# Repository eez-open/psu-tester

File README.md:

PCB tester for H24005 power supply's Power board r5B12 (or later) and AUX power module that can be used during PCBA and final quality assurance process. Require [Arduino Leonardo](https://www.arduino.cc/en/Main/ArduinoBoardLeonardo) board (attached on the opposite side of the PCB) and sketch with various test cases.

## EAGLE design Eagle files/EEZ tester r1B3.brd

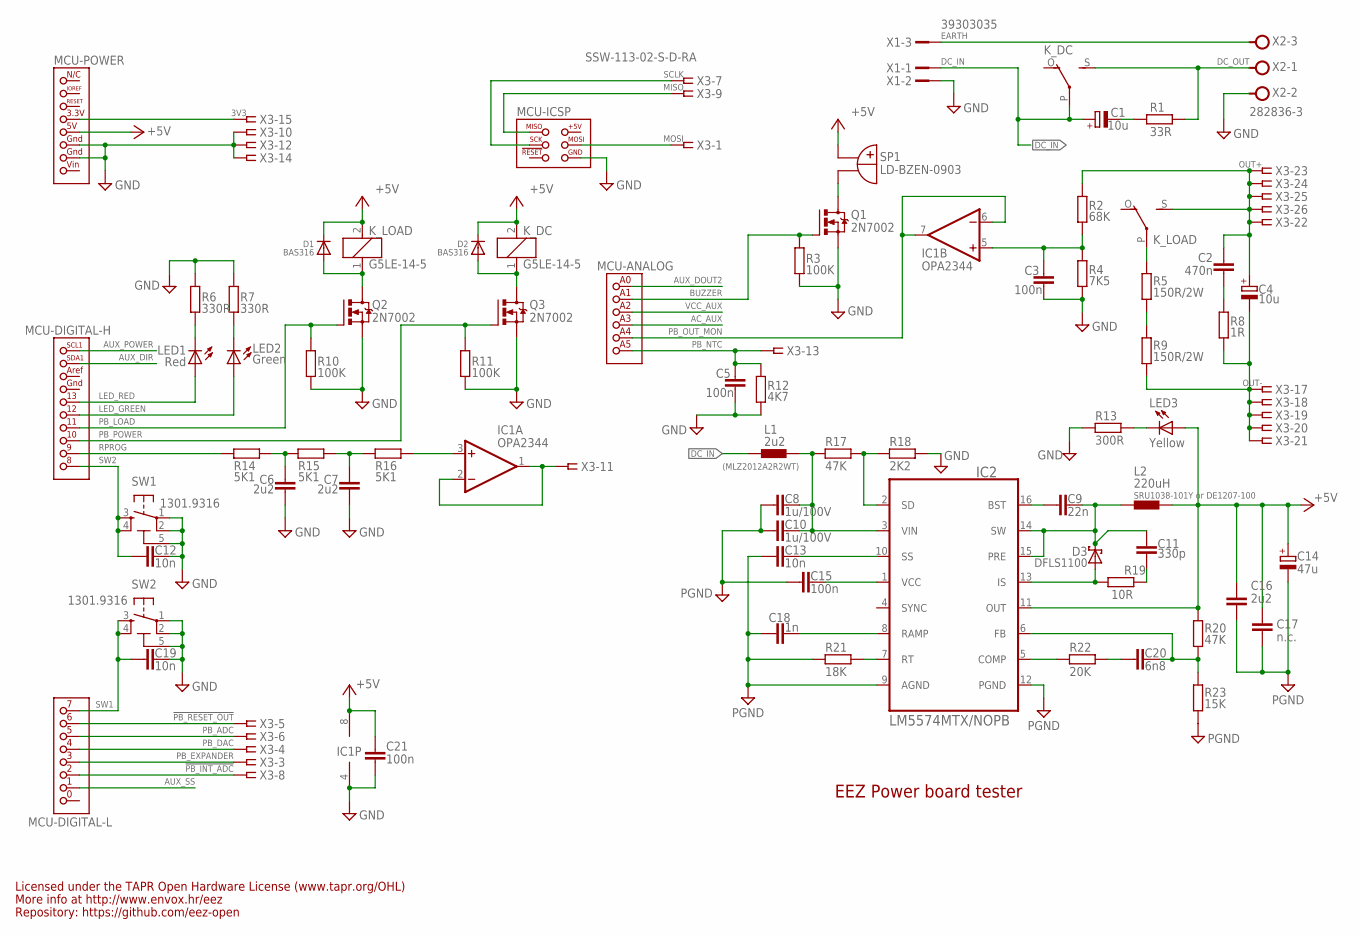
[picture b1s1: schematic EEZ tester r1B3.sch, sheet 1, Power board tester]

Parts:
C1, C4: 10u; PANASONIC_C
C2: 470n; C0805
C3, C5, C15, C21: 100n; C0603
C6, C7, C16: 2u2; C0805
C8, C10: 1u/100V; C1206
C9: 22n; C0805
C11: 330p; C0805
C12, C13, C19: 10n; C0805
C14: 47u; CAPAE660X610N
C17: n.c.; C0805
C18: 1n; C0805
C20: 6n8; C0805
D1, D2: BAS316; SOD323-W
D3: DFLS1100; SOD123
IC1: OPA2344; SOIC127P600X173-8N
IC2: LM5574MTX/NOPB; SOP65P640X110-16N
K_DC: G5LE-14-5; G5LE
K_LOAD: G5LE-14-5; G5LE
L1: 2u2; 0805
L2: 220uH; MSS1278
LED1: Red; LED3MM
LED2: Green; LED3MM
LED3: Yellow; LED3MM
MCU: ARDUINO_LEONARDO
Q1: 2N7002; SOT103P240X110-3N
Q2, Q3: 2N7002; SOT103P240X110-3N; MPN 2N7002-7-F
R1: 33R; R0805
R2: 68K; R0805
R3, R10, R11: 100K; R0805
R4: 7K5; R0805
R5, R9: 150R/2W; 0617/22
R6, R7: 330R; R0805
R8: 1R; R0805
R12: 4K7; R0805
R13: 300R; R0805
R14, R15, R16: 5K1; R0805
R17, R20: 47K; R0805
R18: 2K2; R0805
R19: 10R; R1206
R21: 18K; R0805
R22: 20K; R0805
R23: 15K; R0805
SP1: LD-BZEN-0903
SW1, SW2: 1301.9316; TACTM-6XN
X1: 39303035; MINIFIT_6659-3
X2: 282836-3; TBLOCK5.0_3
X3: SSW-113-02-S-D-RA; TSW-113-02-S-D-RA

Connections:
3V3: MCU.3.3V (3V3), X3.15
!PB_INT_ADC: MCU.2 (2(PE4)), X3.8
!PB_RESET_OUT: MCU.6 (6(PH3)), X3.5
+5V: C14.1 (+), C16.1, C17.1, C21.1, D1.C, D2.C, IC1.8 (V+), IC2.11 (OUT), K_DC.2, K_LOAD.2, L2.2, LED3.A, MCU.5V, R20.1, SP1.+B (+); also elsewhere on the board
AC_AUX: MCU.A3 (ADC3); also elsewhere on the board
AUX_DIR: MCU.SDA1; also elsewhere on the board
AUX_DOUT2: MCU.A0 (ADC0); also elsewhere on the board
AUX_POWER: MCU.SCL1; also elsewhere on the board
AUX_SS: MCU.1 (1(PE1)); also elsewhere on the board
AUX_USET: IC1.1 (OUT), IC1.2 (-IN), X3.11
BUZZER: MCU.A1 (ADC1), Q1.1 (G), R3.2
DC_IN: C1.1 (+), K_DC.P, L1.1, X1.1
DC_OUT: K_DC.S, R1.2, X2.1
DC_PREG1: C8.1, C10.1, IC2.3 (VIN), L1.2, R17.2
EARTH: X1.3, X2.3
GND: C3.1, C5.1, C6.2, C7.2, C8.2, C10.2, C12.2, C13.2, C14.2 (-), C15.1, C16.2, C17.2, C18.1, C19.2, C21.2, IC1.4 (V-), IC2.9 (AGND), IC2.12 (PGND), MCU.GND1, MCU.GND2, MCU.ICSP_GND (GND), Q1.2 (S), Q2.2 (S), Q3.2 (S), R3.1, R4.2, R6.2, R7.2, R10.1, R11.1, R12.2, R13.1, R18.1, R21.2, R23.2, SW1.1, SW1.2, SW1.5 (5-GND), SW2.1, SW2.2, SW2.5 (5-GND), X1.2, X2.2, X3.10, X3.12, X3.14; also elsewhere on the board
IS: D3.A, IC2.13 (IS), R19.1
LED_GREEN: LED2.A, MCU.12
LED_RED: LED1.A, MCU.13
MISO: MCU.ICSP_MISO (MISO), X3.9
MOSI: MCU.ICSP_MOSI (MOSI), X3.1
unnamed: R5.1, R9.2
unnamed: K_LOAD.P, R5.2
unnamed: LED3.K (C), R13.2
unnamed: C1.2 (-), R1.1
unnamed: C3.2, IC1.5 (+IN), R2.2, R4.1
unnamed: C7.1, R15.1, R16.2
unnamed: Q1.3 (D), SP1.-B (-)
unnamed: C6.1, R14.1, R15.2
unnamed: LED1.K (C), R6.1
unnamed: LED2.K (C), R7.1
unnamed: D2.A, K_DC.1, Q3.3 (D)
unnamed: D1.A, K_LOAD.1, Q2.3 (D)
unnamed: C11.2, R19.2
unnamed: C20.2, R22.2
unnamed: C2.2, R8.2
unnamed: C20.1, IC2.6 (FB), R20.2, R23.1
unnamed: C9.2, IC2.16 (BST)
unnamed: IC2.5 (COMP), R22.1
unnamed: IC2.7 (RT), R21.1
unnamed: C15.2, IC2.1 (VCC)
unnamed: C18.2, IC2.8 (RAMP)
unnamed: C13.1, IC2.10 (SS)
unnamed: IC2.2 (SD), R17.1, R18.2
unnamed: IC1.3 (+IN), R16.1
OUT+: C2.1, C4.1 (+), K_LOAD.S, R2.1, X3.22, X3.23, X3.24, X3.25, X3.26
OUT-: C4.2 (-), R8.1, R9.1, X3.17, X3.18, X3.19, X3.20, X3.21
PB_ADC: MCU.5 (5(PE3)), X3.6
PB_DAC: MCU.4 (4(PG5)), X3.4
PB_EXPANDER: MCU.3 (3(PE5)), X3.3
PB_LOAD: MCU.11, Q2.1 (G), R10.2
PB_NTC: C5.2, MCU.A5 (ADC5), R12.1, X3.13
PB_OUT_MON: IC1.6 (-IN), IC1.7 (OUT), MCU.A4 (ADC4)
PB_POWER: MCU.10, Q3.1 (G), R11.2
RPROG: MCU.9 (9(PH6)), R14.2
SCLK: MCU.ICSP_SCK (SCK), X3.7
SW: C9.1, C11.1, D3.C, IC2.14 (SW), IC2.15 (PRE), L2.1
SW1: C19.1, MCU.7 (7(PH4)), SW2.3, SW2.4
SW2: C12.1, MCU.8 (8(PH5)), SW1.3, SW1.4
VCC_AUX: MCU.A2 (ADC2); also elsewhere on the board

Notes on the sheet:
EEZ Power board tester
Licensed under the TAPR Open Hardware License (www.tapr.org/OHL)
Repository: https://github.com/eez-open
More info at http://www.envox.hr/eez
(MLZ2012A2R2WT)
SRU1038-101Y or DE1207-100

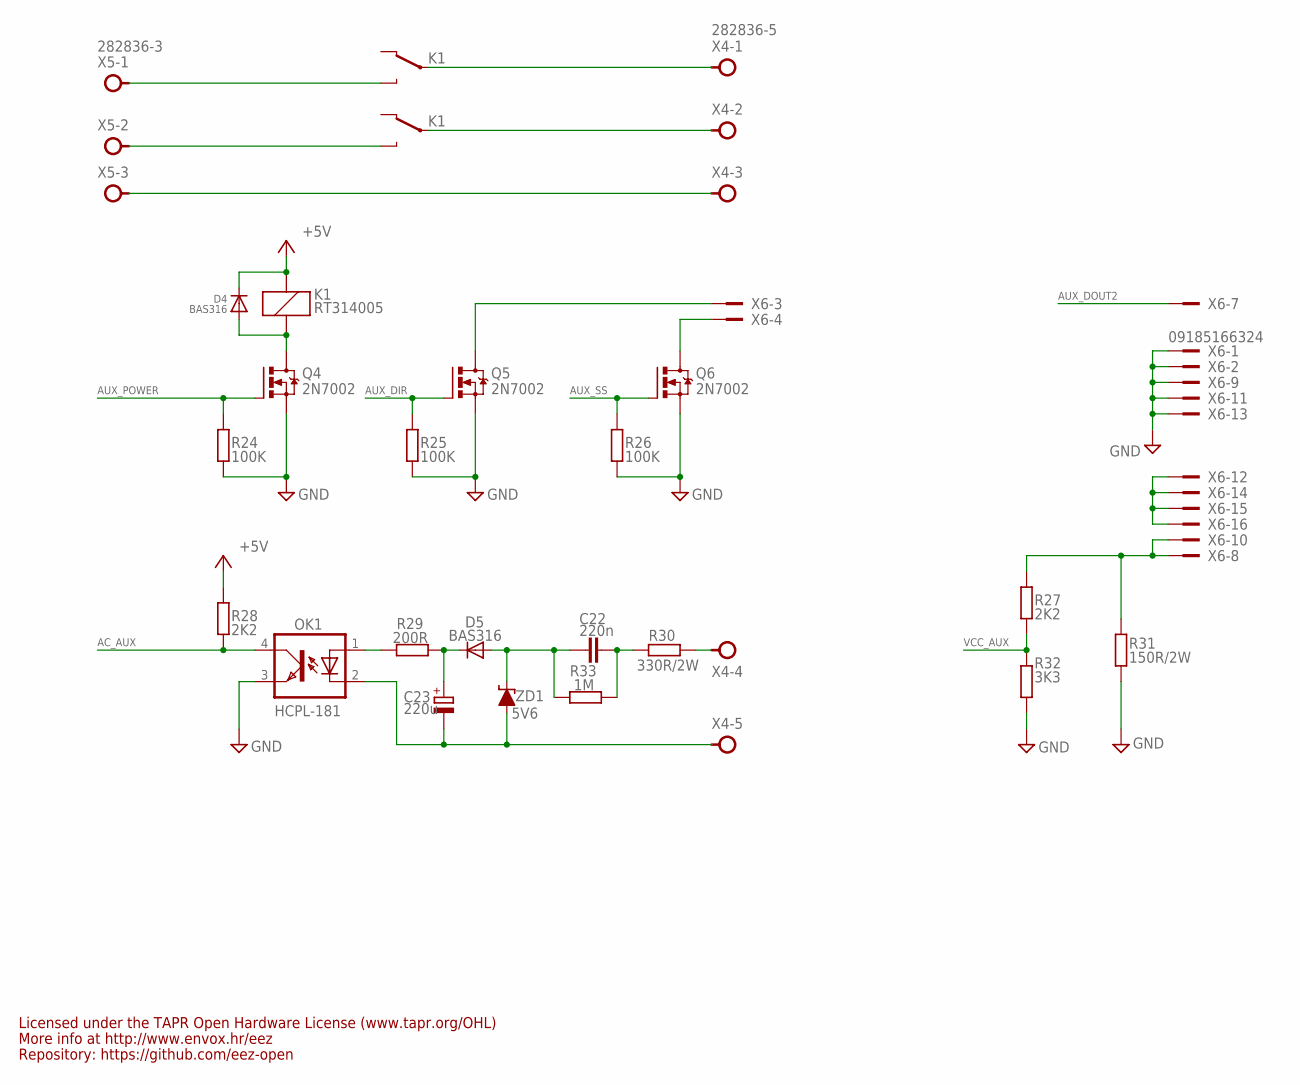
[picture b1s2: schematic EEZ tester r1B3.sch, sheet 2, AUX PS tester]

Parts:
C22: 220n; C150-084X183
C23: 220u; CAPAE660X610N
D4, D5: BAS316; SOD323-W
K1: RT314005; RT-C/016A5_ROUND
OK1: HCPL-181
Q4, Q5, Q6: 2N7002; SOT103P240X110-3N; MPN 2N7002-7-F
R24, R25, R26: 100K; R0805
R27, R28: 2K2; R0805
R29: 200R; R0805
R30: 330R/2W; R2512
R31: 150R/2W; R2512
R32: 3K3; R0805
R33: 1M; R0805
X4: 282836-5; TBLOCK5.0_5
X5: 282836-3; TBLOCK5.0_3
X6: 09185166324; IDC-16PIN
ZD1: 5V6; SOD323-W

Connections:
+5V: D4.C, K1.A2 (C1), R28.2; also elsewhere on the board
AC_AUX: OK1.4 (COL), R28.1; also elsewhere on the board
AUX_DIR: Q5.1 (G), R25.2; also elsewhere on the board
AUX_DOUT2: X6.7; also elsewhere on the board
AUX_POWER: Q4.1 (G), R24.2; also elsewhere on the board
AUX_SS: Q6.1 (G), R26.2; also elsewhere on the board
GND: OK1.3 (EMIT), Q4.2 (S), Q5.2 (S), Q6.2 (S), R24.1, R25.1, R26.1, R31.2, R32.1, X6.1, X6.2, X6.9, X6.11, X6.13; also elsewhere on the board
unnamed: Q5.3 (D), X6.3
unnamed: K1.11A, X4.2
unnamed: D4.A, K1.A1 (C2), Q4.3 (D)
unnamed: K1.11B, X4.1
unnamed: K1.14B (O), X5.1
unnamed: K1.14A (O), X5.2
unnamed: X4.3, X5.3
unnamed: R30.1, X4.4
unnamed: C22.2, R30.2, R33.1
unnamed: C22.1, D5.A, R33.2, ZD1.C
unnamed: C23.2 (-), OK1.2 (C), X4.5, ZD1.A
unnamed: Q6.3 (D), X6.4
unnamed: OK1.1 (A), R29.2
unnamed: C23.1 (+), D5.C, R29.1
unnamed: R27.2, R31.1, X6.8, X6.10
unnamed: X6.12, X6.14, X6.15, X6.16
VCC_AUX: R27.1, R32.2; also elsewhere on the board

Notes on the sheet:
Licensed under the TAPR Open Hardware License (www.tapr.org/OHL)
Repository: https://github.com/eez-open
More info at http://www.envox.hr/eez

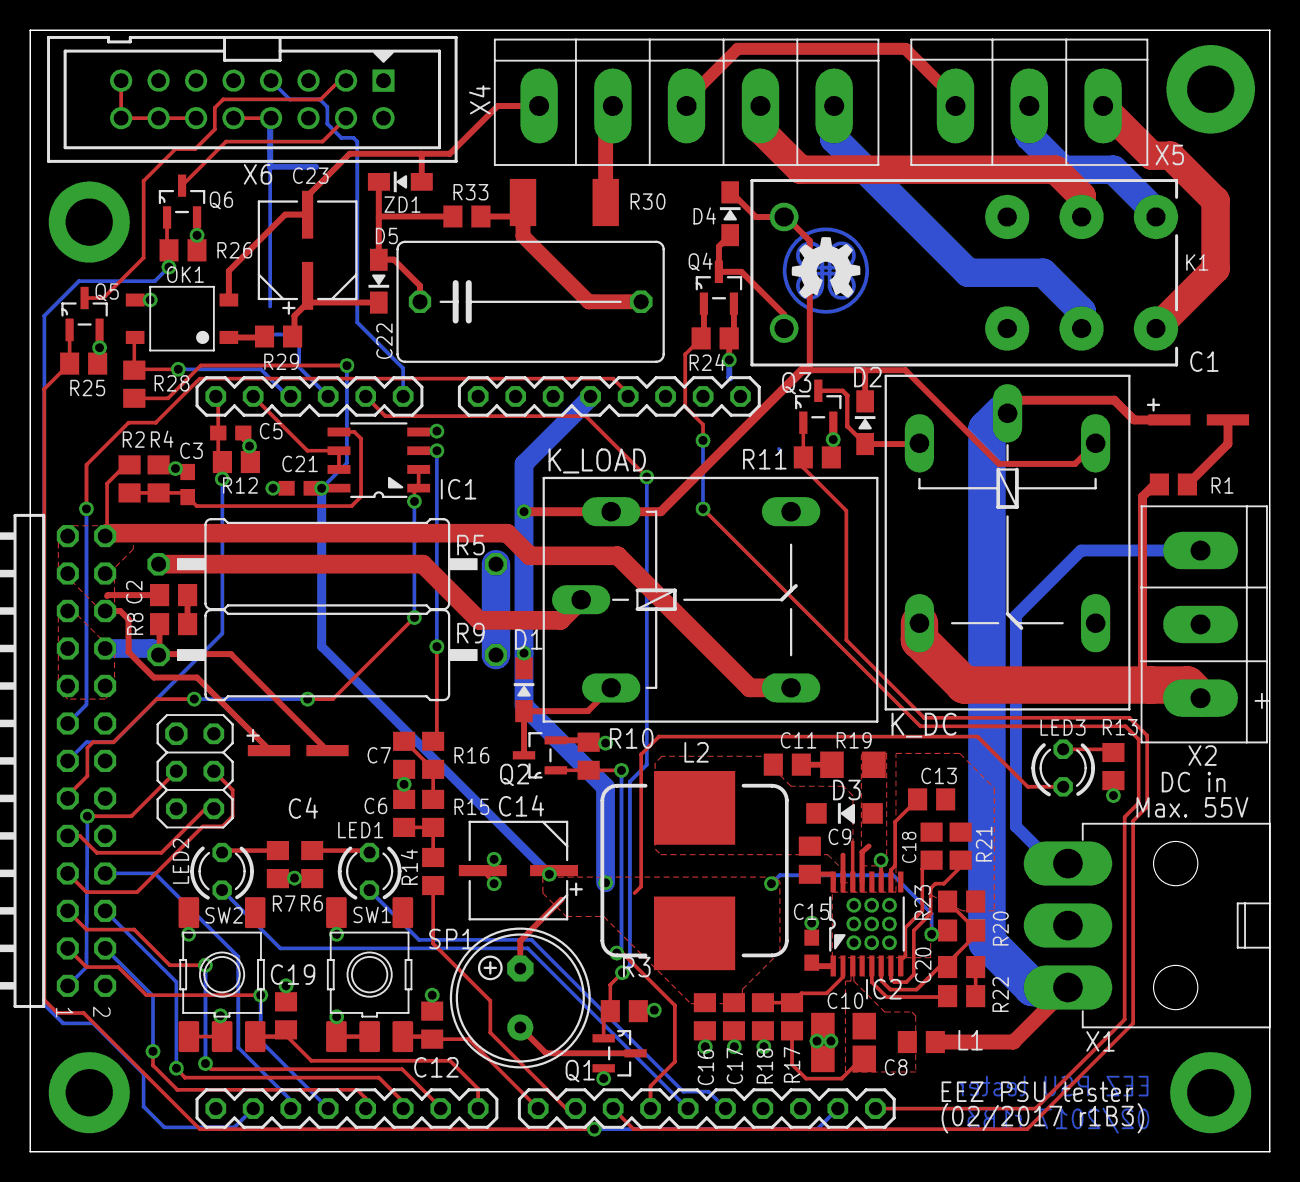
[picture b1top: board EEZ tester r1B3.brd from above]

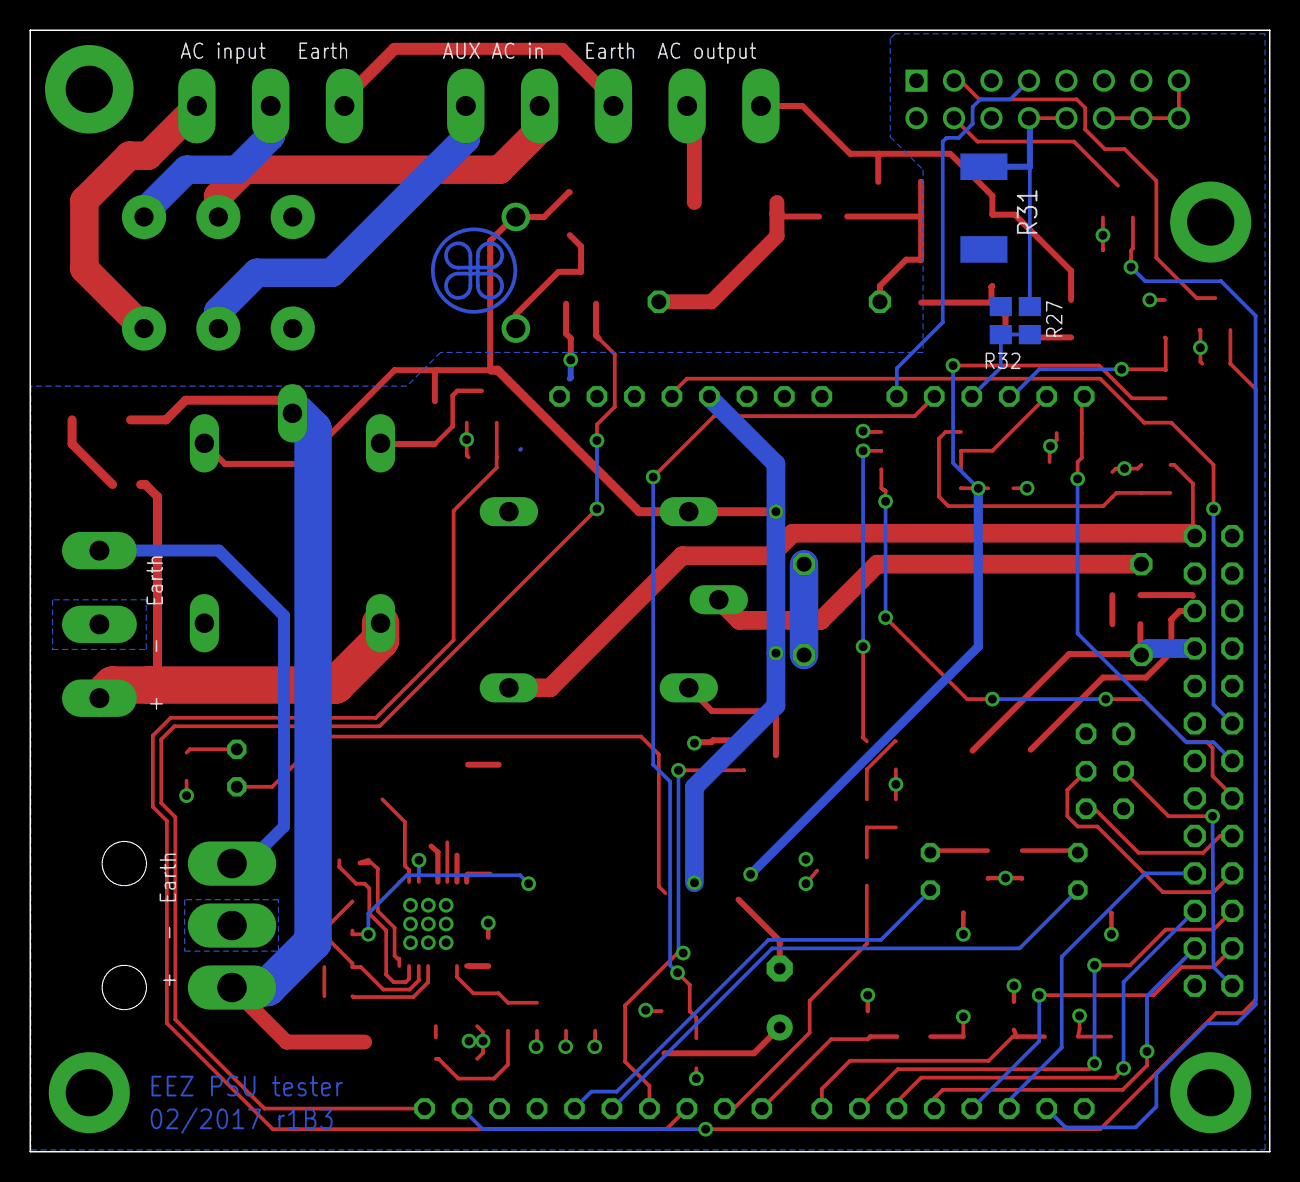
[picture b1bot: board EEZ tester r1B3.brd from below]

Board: 2 copper layers, 84.0 x 76.0 mm, 90 parts (3 on the bottom side), 76 nets.

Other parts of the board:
EEZ_SIGNATURE2: SIGNATURESMALL; SIGNATURE_5MM

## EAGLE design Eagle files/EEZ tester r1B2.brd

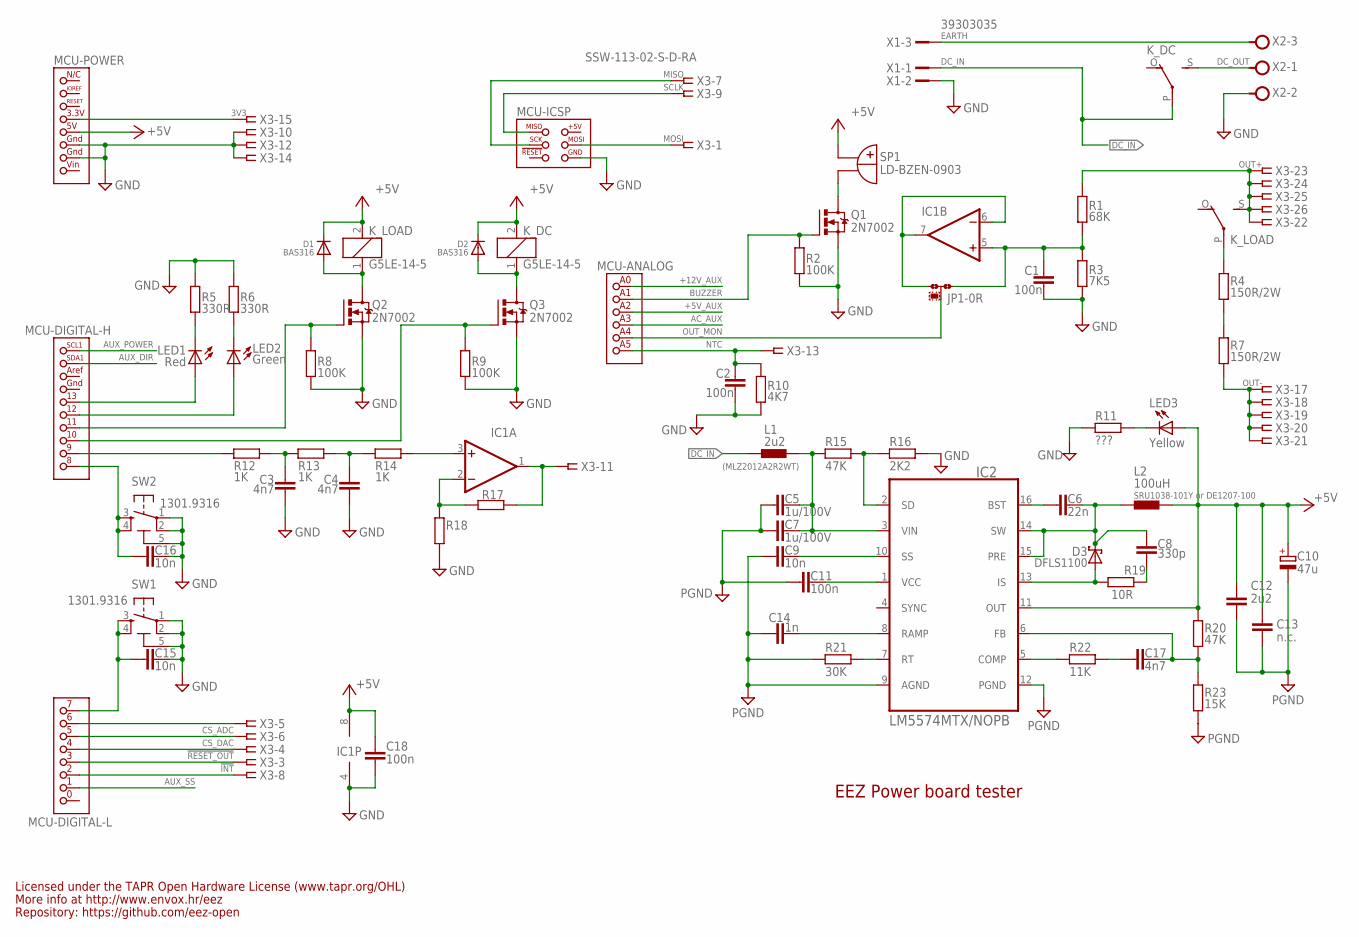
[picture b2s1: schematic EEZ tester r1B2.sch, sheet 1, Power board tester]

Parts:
C1, C2, C11, C18: 100n; C0603
C3, C4, C17: 4n7; C0805
C5, C7: 1u/100V; C1206
C6: 22n; C0805
C8: 330p; C0805
C9, C15, C16: 10n; C0805
C10: 47u; CAPAE660X610N
C12: 2u2; C0805
C13: n.c.; C0805
C14: 1n; C0805
D1, D2: BAS316; SOD323-W
D3: DFLS1100; SOD123
IC1: TL072SOIC8; SOIC127P600X173-8N
IC2: LM5574MTX/NOPB; SOP65P640X110-16N
JP1: 0R-JUMPA; A0R-JMP
K_DC: G5LE-14-5; G5LE
K_LOAD: G5LE-14-5; G5LE
L1: 2u2; 0805
L2: 100uH; MSS1278
LED1: Red; LED3MM
LED2: Green; LED3MM
LED3: Yellow; LED3MM
MCU: ARDUINO_LEONARDO
Q1: 2N7002; SOT103P240X110-3N
Q2, Q3: 2N7002; SOT103P240X110-3N; MPN 2N7002-7-F
R1: 68K; R0805
R2, R8, R9: 100K; R0805
R3: 7K5; R0805
R4, R7: 150R/2W; 0617/22
R5, R6: 330R; R0805
R10: 4K7; R0805
R11: ???; R0805
R12, R13, R14: 1K; R0805
R15, R20: 47K; R0805
R16: 2K2; R0805
R17, R18: R-EU_R0805; R0805
R19: 10R; R1206
R21: 30K; R0805
R22: 11K; R0805
R23: 15K; R0805
SP1: LD-BZEN-0903
SW1, SW2: 1301.9316; TACTM-6XN
X1: 39303035; MINIFIT_6659-3
X2: TBLOCK5.0_3A; TBLOCK5.0_3
X3: SSW-113-02-S-D-RA; TSW-113-02-S-D-RA

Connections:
3V3: MCU.3.3V (3V3), X3.15
!INT: MCU.2 (2(PE4)), X3.8
!RESET_OUT: MCU.3 (3(PE5)), X3.3
+5V: C10.1 (+), C12.1, C13.1, C18.1, D1.C, D2.C, IC1.8 (V+), IC2.11 (OUT), K_DC.2, K_LOAD.2, L2.2, LED3.A, MCU.5V, R20.1, SP1.+B (+); also elsewhere on the board
+5V_AUX: MCU.A2 (ADC2); also elsewhere on the board
+12V_AUX: MCU.A0 (ADC0); also elsewhere on the board
AC_AUX: MCU.A3 (ADC3); also elsewhere on the board
AUX_DIR: MCU.SDA1; also elsewhere on the board
AUX_POWER: MCU.SCL1; also elsewhere on the board
AUX_SS: MCU.1 (1(PE1)); also elsewhere on the board
AUX_USET: IC1.1 (OUT), R17.2, X3.11
BUZZER: MCU.A1 (ADC1), Q1.1 (G), R2.2
CS_ADC: MCU.5 (5(PE3)), X3.6
CS_DAC: MCU.4 (4(PG5)), X3.4
CS_EXPANDER: MCU.6 (6(PH3)), X3.5
DC_IN: K_DC.P, L1.1, X1.1
DC_OUT: K_DC.S, X2.1
DC_PREG1: C5.1, C7.1, IC2.3 (VIN), L1.2, R15.2
EARTH: X1.3, X2.3
GND: C1.1, C2.1, C3.2, C4.2, C5.2, C7.2, C9.2, C10.2 (-), C11.1, C12.2, C13.2, C14.1, C15.2, C16.2, C18.2, IC1.4 (V-), IC2.9 (AGND), IC2.12 (PGND), MCU.GND1, MCU.GND2, MCU.ICSP_GND (GND), Q1.2 (S), Q2.2 (S), Q3.2 (S), R2.1, R3.2, R5.2, R6.2, R8.1, R9.1, R10.2, R11.1, R16.1, R18.2, R21.2, R23.2, SW1.1, SW1.2, SW1.5 (5-GND), SW2.1, SW2.2, SW2.5 (5-GND), X1.2, X2.2, X3.10, X3.12, X3.14; also elsewhere on the board
IS: D3.A, IC2.13 (IS), R19.1
MISO: MCU.ICSP_SCK (SCK), X3.7
MOSI: MCU.ICSP_MOSI (MOSI), X3.1
unnamed: R4.1, R7.2
unnamed: K_LOAD.P, R4.2
unnamed: LED3.K (C), R11.2
unnamed: IC1.6 (-IN), IC1.7 (OUT), JP1.3
unnamed: MCU.9 (9(PH6)), R12.2
unnamed: C1.2, IC1.5 (+IN), JP1.1, R1.2, R3.1
unnamed: MCU.11, Q2.1 (G), R8.2
unnamed: C4.1, R13.1, R14.2
unnamed: Q1.3 (D), SP1.-B (-)
unnamed: C15.1, MCU.7 (7(PH4)), SW1.3, SW1.4
unnamed: LED2.A, MCU.12
unnamed: C3.1, R12.1, R13.2
unnamed: LED1.A, MCU.13
unnamed: LED1.K (C), R5.1
unnamed: LED2.K (C), R6.1
unnamed: C16.1, MCU.8 (8(PH5)), SW2.3, SW2.4
unnamed: MCU.10, Q3.1 (G), R9.2
unnamed: D2.A, K_DC.1, Q3.3 (D)
unnamed: D1.A, K_LOAD.1, Q2.3 (D)
unnamed: C8.2, R19.2
unnamed: C17.2, R22.2
unnamed: C17.1, IC2.6 (FB), R20.2, R23.1
unnamed: C6.2, IC2.16 (BST)
unnamed: IC2.5 (COMP), R22.1
unnamed: IC2.7 (RT), R21.1
unnamed: C11.2, IC2.1 (VCC)
unnamed: C14.2, IC2.8 (RAMP)
unnamed: C9.1, IC2.10 (SS)
unnamed: IC2.2 (SD), R15.1, R16.2
unnamed: IC1.2 (-IN), R17.1, R18.1
unnamed: IC1.3 (+IN), R14.1
NTC: C2.2, MCU.A5 (ADC5), R10.1, X3.13
OUT+: K_LOAD.S, R1.1, X3.22, X3.23, X3.24, X3.25, X3.26
OUT-: R7.1, X3.17, X3.18, X3.19, X3.20, X3.21
OUT_MON: JP1.2, MCU.A4 (ADC4)
SCLK: MCU.ICSP_MISO (MISO), X3.9
SW1: C6.1, C8.1, D3.C, IC2.14 (SW), IC2.15 (PRE), L2.1

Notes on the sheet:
EEZ Power board tester
Licensed under the TAPR Open Hardware License (www.tapr.org/OHL)
Repository: https://github.com/eez-open
More info at http://www.envox.hr/eez
(MLZ2012A2R2WT)
SRU1038-101Y or DE1207-100

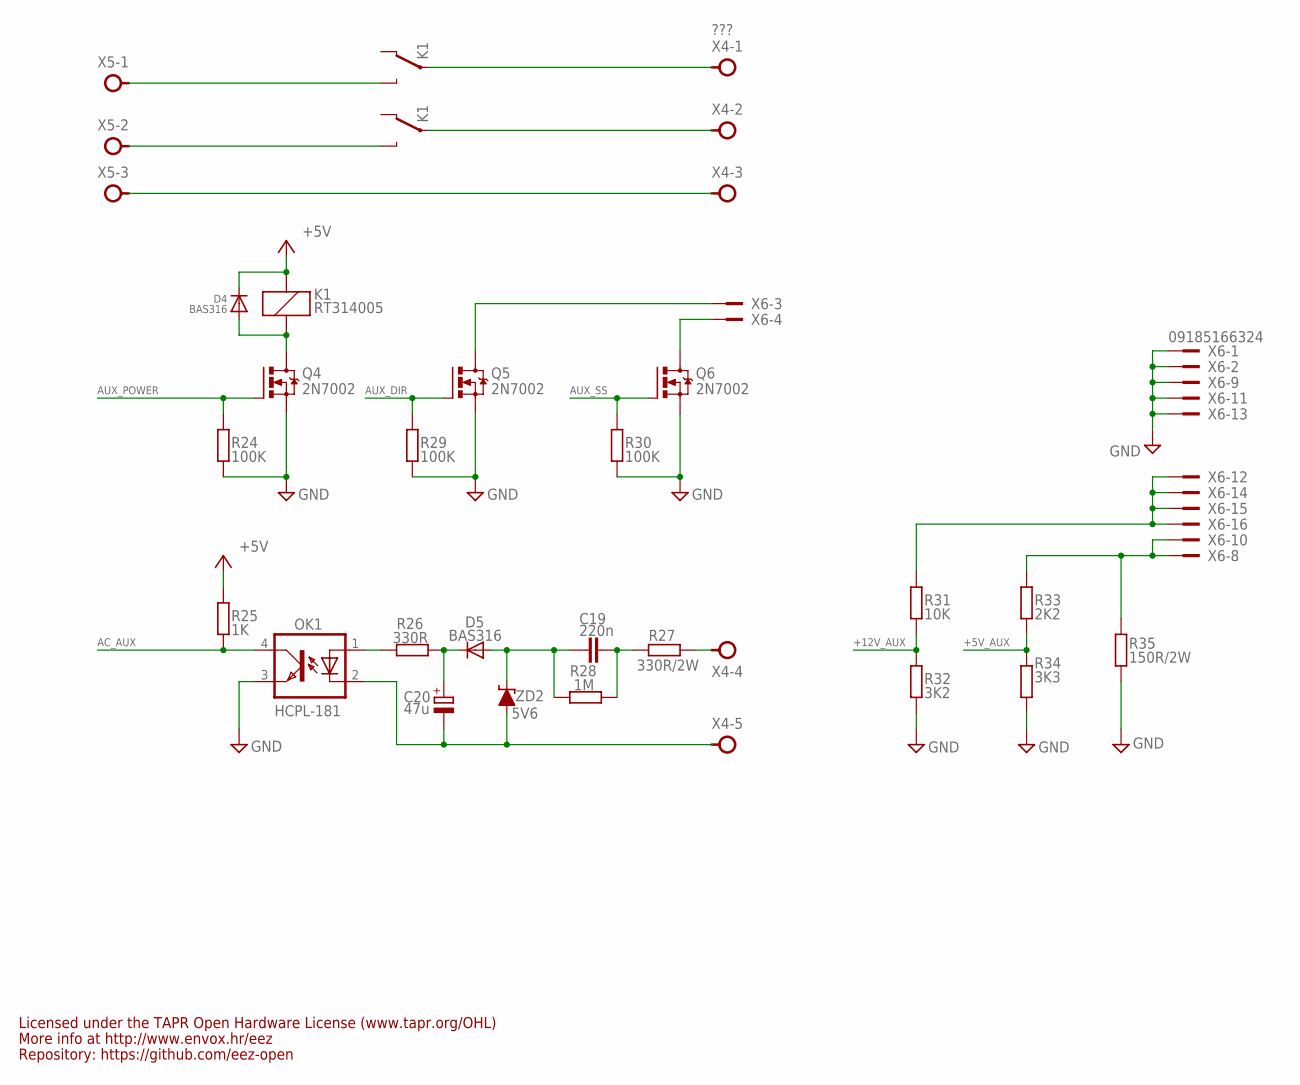
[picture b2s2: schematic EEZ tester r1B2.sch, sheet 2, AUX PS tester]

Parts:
C19: 220n; C150-084X183
C20: 47u; CAPAE660X610N
D4, D5: BAS316; SOD323-W
K1: RT314005; RT-C/016A5_ROUND
OK1: HCPL-181
Q4, Q5, Q6: 2N7002; SOT103P240X110-3N; MPN 2N7002-7-F
R24, R29, R30: 100K; R0805
R25: 1K; R0805
R26: 330R; R0805
R27: 330R/2W; R2512
R28: 1M; R0805
R31: 10K; R0805
R32: 3K2; R0805
R33: 2K2; R0805
R34: 3K3; R0805
R35: 150R/2W; R2512
X4: ???; TBLOCK5.0_5
X5: TBLOCK5.0_3A; TBLOCK5.0_3
X6: 09185166324; IDC-16PIN
ZD2: 5V6; SOD323-W

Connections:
+5V: D4.C, K1.A2 (C1), R25.2; also elsewhere on the board
+5V_AUX: R33.1, R34.2; also elsewhere on the board
+12V_AUX: R31.1, R32.2; also elsewhere on the board
AC_AUX: OK1.4 (COL), R25.1; also elsewhere on the board
AUX_DIR: Q5.1 (G), R29.2; also elsewhere on the board
AUX_POWER: Q4.1 (G), R24.2; also elsewhere on the board
AUX_SS: Q6.1 (G), R30.2; also elsewhere on the board
GND: OK1.3 (EMIT), Q4.2 (S), Q5.2 (S), Q6.2 (S), R24.1, R29.1, R30.1, R32.1, R34.1, R35.2, X6.1, X6.2, X6.9, X6.11, X6.13; also elsewhere on the board
unnamed: Q5.3 (D), X6.3
unnamed: D4.A, K1.A1 (C2), Q4.3 (D)
unnamed: K1.11B, X4.1
unnamed: K1.14B (O), X5.1
unnamed: K1.14A (O), X5.2
unnamed: K1.11A, X4.2
unnamed: X4.3, X5.3
unnamed: R27.1, X4.4
unnamed: C19.2, R27.2, R28.1
unnamed: C19.1, D5.A, R28.2, ZD2.C
unnamed: C20.2 (-), OK1.2 (C), X4.5, ZD2.A
unnamed: Q6.3 (D), X6.4
unnamed: OK1.1 (A), R26.2
unnamed: C20.1 (+), D5.C, R26.1
unnamed: R33.2, R35.1, X6.8, X6.10
unnamed: R31.2, X6.12, X6.14, X6.15, X6.16

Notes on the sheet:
Licensed under the TAPR Open Hardware License (www.tapr.org/OHL)
Repository: https://github.com/eez-open
More info at http://www.envox.hr/eez

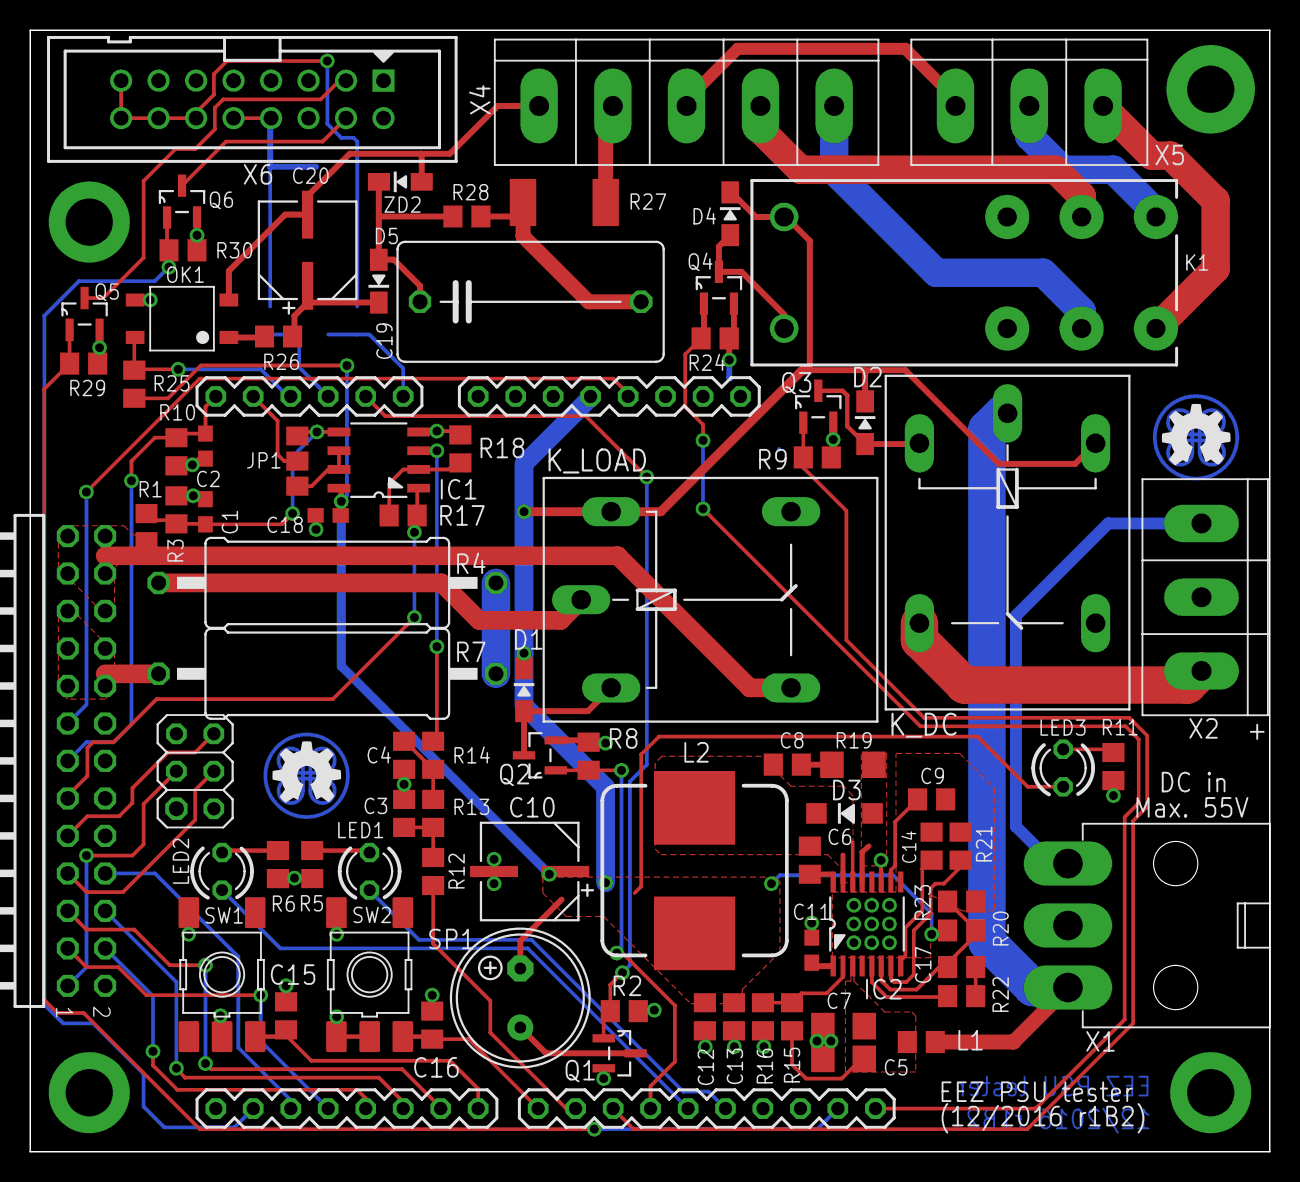
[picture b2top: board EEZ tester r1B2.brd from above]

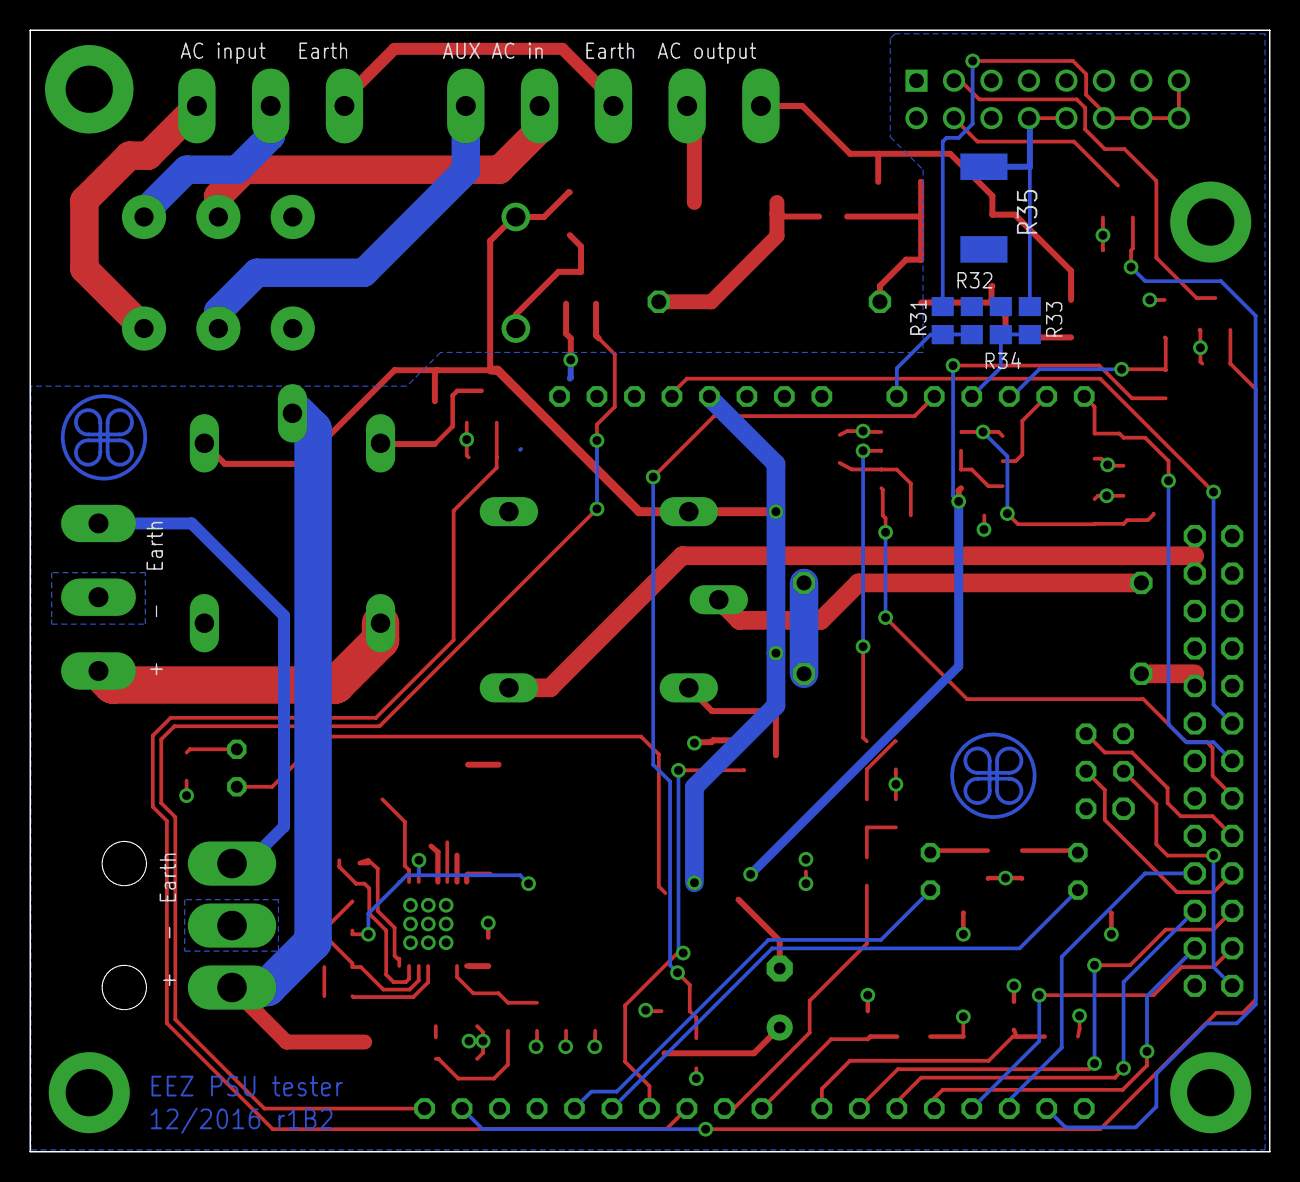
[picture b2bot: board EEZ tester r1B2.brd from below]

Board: 2 copper layers, 84.0 x 76.0 mm, 91 parts (5 on the bottom side), 76 nets.

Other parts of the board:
EEZ_SIGNATURE, EEZ_SIGNATURE2: SIGNATURESMALL; SIGNATURE_5MM

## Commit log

2016-12-27 inital push
2016-12-27 PCB layout pictures
2016-12-27 Eagle and license files
2017-01-22 Arduino rotated ICSP fixed
2017-01-22 parts value corrections
2017-01-31 few pictures added
2017-02-02 pinout redefinition
2017-08-21 README.md pic fixed
2017-08-21 reset file permissions
